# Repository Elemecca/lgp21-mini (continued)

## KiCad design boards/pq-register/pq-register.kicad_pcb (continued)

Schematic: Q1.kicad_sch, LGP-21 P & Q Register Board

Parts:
C27, C30: 120p; C_0402_1005Metric
C28, C29: 680p; C_0402_1005Metric
CR13, CR14: 1N5819WS; D_SOD-323
Q57, Q58, Q59, Q60, Q61, Q62, Q64, Q66, Q67, Q68, Q69, Q70, Q71, Q72: MMBT5401; SOT-23
R268, R270, R272, R274, R276, R278, R283, R287, R289, R291, R293, R295: 56k; R_0402_1005Metric
R269, R271, R273, R275, R277, R279, R284, R288, R290, R292, R294, R296: 2k 500mW; R_1210_3225Metric
R297, R298: 33k; R_0402_1005Metric
R310, R311, R312, R313, R314, R315, R316, R317, R318, R319, R320, R321, R322, R323, R324, R325, R326, R327, R328, R329, R330, R331, R332, R333, R340, R341, R342, R351, R352, R353, R354, R355, R356, R357, R358, R359, R360, R361: 15k; R_0402_1005Metric
R350, R362, R363, R364: 2k4; R_0402_1005Metric
R382, R502: 300R 3W; R_Axial_DIN0516_L15.5mm_D5.0mm_P20.32mm_Horizontal
R447, R506: 15k; R_0402_1005Metric; not fitted

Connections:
+15V: R268.2, R270.2, R272.2, R274.2, R276.2, R278.2, R283.2, R287.2, R289.2, R291.2, R293.2, R295.2, R297.2, R298.2; also elsewhere on the board
-20V: R269.1, R271.1, R273.1, R275.1, R277.1, R279.1, R284.1, R288.1, R290.1, R292.1, R294.1, R296.1, R382.1; also elsewhere on the board
-20V_{D}: R502.1; also elsewhere on the board
/Q1/Q1': Q66.3 (C), R288.2, R350.1
/Q1/~Q1': Q70.3 (C), R296.2, R362.2
CP_{2}: C28.2, C29.2; also elsewhere on the board
G: R327.1, R356.1; also elsewhere on the board
GND: Q57.2 (E), Q58.2 (E), Q59.2 (E), Q60.2 (E), Q61.2 (E), Q62.2 (E), Q64.2 (E), Q66.2 (E), Q67.2 (E), Q68.2 (E), Q69.2 (E), Q70.2 (E), Q71.2 (E), Q72.2 (E); also elsewhere on the board
unnamed: C28.1, CR13.2 (A), R362.1
unnamed: C27.1, CR13.1 (K), Q71.1 (B), R297.1, R363.2
unnamed: C29.1, CR14.2 (A), R350.2
unnamed: C30.2, CR14.1 (K), Q72.1 (B), R298.1, R364.1
unnamed: Q57.1 (B), R268.1, R310.2, R311.2
unnamed: Q57.3 (C), R269.2, R312.1
unnamed: Q58.1 (B), R270.1, R313.2, R314.2
unnamed: Q58.3 (C), R271.2, R315.1
unnamed: Q59.1 (B), R272.1, R316.2, R317.2
unnamed: Q59.3 (C), R273.2, R318.1
unnamed: Q60.1 (B), R274.1, R319.2, R320.2
unnamed: Q60.3 (C), R275.2, R321.1
unnamed: Q61.1 (B), R276.1, R312.2, R315.2, R318.2, R321.2, R322.2
unnamed: Q61.3 (C), R277.2, R324.1
unnamed: Q62.1 (B), R278.1, R323.2, R324.2, R325.2, R326.2, R327.2, R328.2, R329.2, R330.2, R331.2, R333.2
unnamed: Q62.3 (C), R279.2, R332.1
unnamed: Q64.1 (B), R283.1, R340.2, R341.2
unnamed: Q64.3 (C), R284.2, R342.1
unnamed: Q66.1 (B), R287.1, R332.2, R342.2
unnamed: Q67.1 (B), R289.1, R351.2, R352.2
unnamed: Q67.3 (C), R290.2, R322.1
unnamed: Q68.1 (B), R291.1, R353.2, R354.2, R355.2, R356.2, R447.2
unnamed: Q68.3 (C), R292.2, R357.1
unnamed: Q69.1 (B), R293.1, R358.2, R359.2
unnamed: Q69.3 (C), R294.2, R360.1
unnamed: Q70.1 (B), R295.1, R357.2, R360.2, R361.2, R506.2
P1: R310.1; also elsewhere on the board
P2: R313.1; also elsewhere on the board
P3: R316.1; also elsewhere on the board
P4: R319.1; also elsewhere on the board
Q1: C30.1, Q71.3 (C), R355.1, R364.2, R382.2; also elsewhere on the board
Q1b: R447.1; also elsewhere on the board
R: R340.1, R351.1; also elsewhere on the board
T3: R331.1, R353.1; also elsewhere on the board
~C: R352.1; also elsewhere on the board
~Faf: R333.1; also elsewhere on the board
~H: R329.1, R354.1; also elsewhere on the board
~Q1d: R506.1; also elsewhere on the board
~Q1: C27.2, Q72.3 (C), R326.1, R363.1, R502.2; also elsewhere on the board
~Q2: R325.1; also elsewhere on the board
~Q3: R328.1; also elsewhere on the board
~Q4: R330.1; also elsewhere on the board
~R: R358.1; also elsewhere on the board
~Tb1: R311.1; also elsewhere on the board
~Tb2: R314.1; also elsewhere on the board
~Tb3: R317.1; also elsewhere on the board
~Tb4: R320.1; also elsewhere on the board
~To: R323.1; also elsewhere on the board
~bq: R361.1; also elsewhere on the board
α11: R341.1, R359.1; also elsewhere on the board

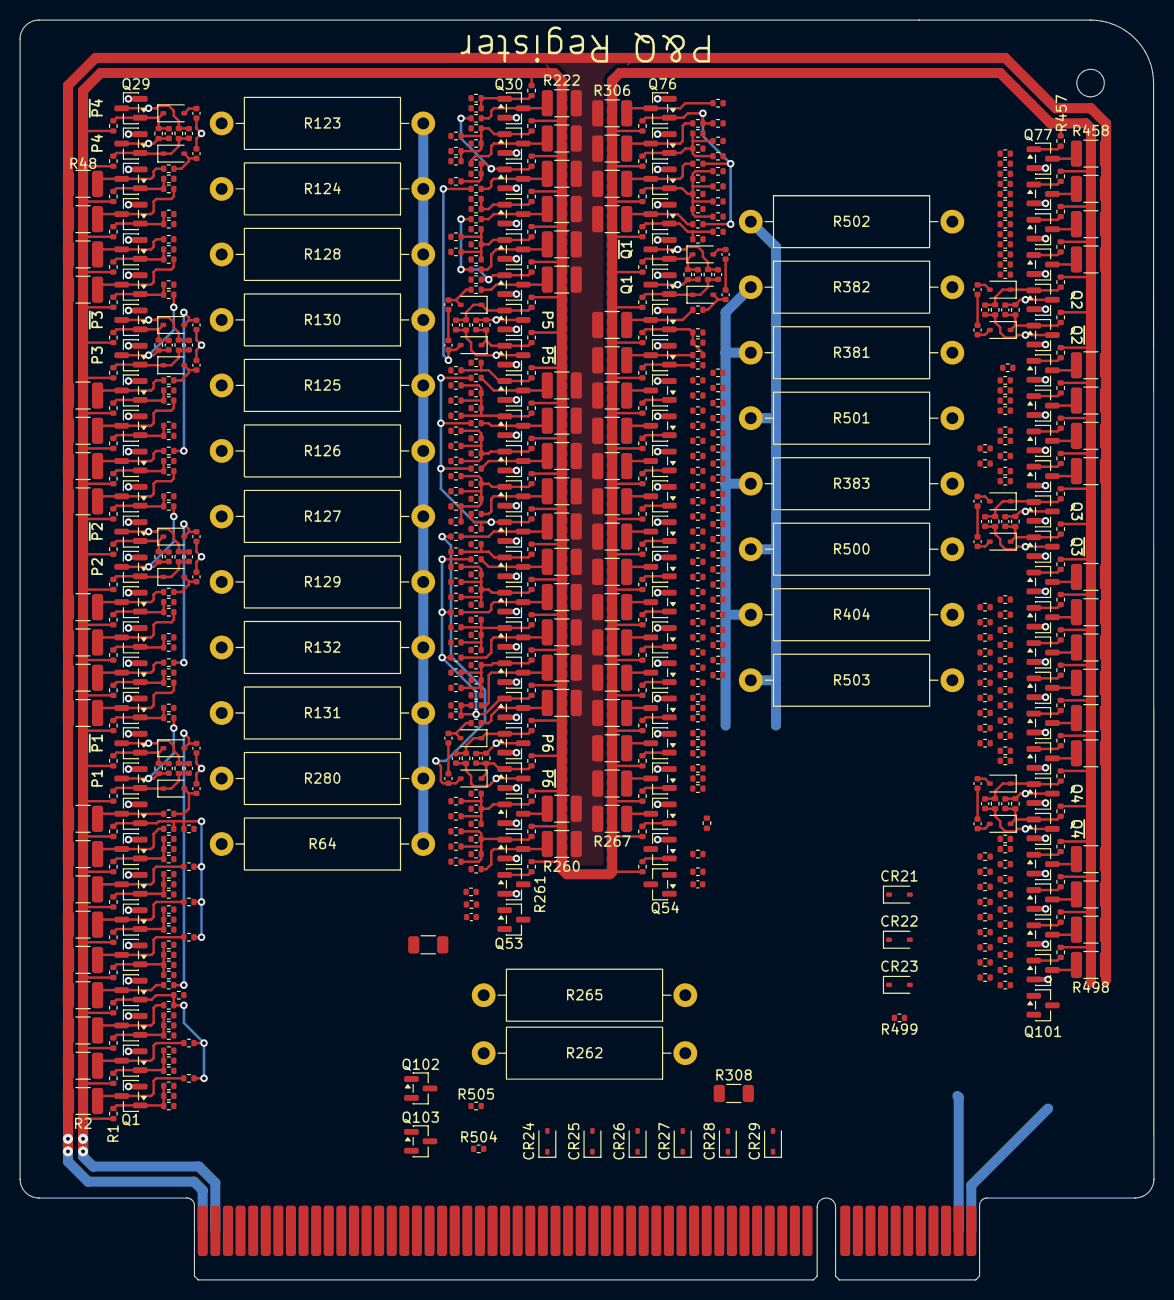
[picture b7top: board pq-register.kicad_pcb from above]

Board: 2 copper layers, 114.3 x 127.0 mm, 689 parts (1 on the bottom side), 291 nets.

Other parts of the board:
MH1: Bivar CP-26 WE; Bivar_CP-26_WE

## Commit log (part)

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2026-06-29 Import PQ Register schematic and do gross layout.
2026-06-30 Densify layout and define board outline.
